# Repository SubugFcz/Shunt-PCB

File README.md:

# Shunt-PCB
Shunt PCB Design for GTSR

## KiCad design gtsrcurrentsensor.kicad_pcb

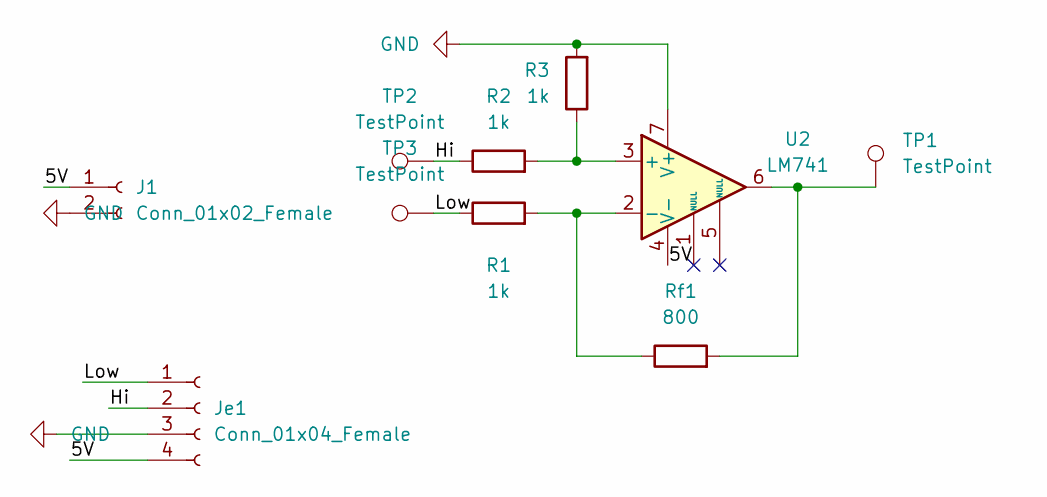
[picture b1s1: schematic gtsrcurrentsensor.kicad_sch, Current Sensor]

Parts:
J1: Conn_01x02_Female; Molex_Micro-Fit_3.0_43650-0215_1x02_P3.00mm_Vertical
Je1: Conn_01x04_Female; Molex_Micro-Fit_3.0_43650-0415_1x04_P3.00mm_Vertical
R1, R2, R3: 1k; R_Axial_DIN0207_L6.3mm_D2.5mm_P7.62mm_Horizontal
Rf1: 800; R_Axial_DIN0207_L6.3mm_D2.5mm_P7.62mm_Horizontal
TP1, TP2, TP3: TestPoint; gtsr-connector-KEYSTONE_5001_0
U2: LM741; DIP-8_W7.62mm

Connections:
/5V: J1.1, Je1.4, U2.4 (V-)
/Hi: Je1.2, R2.1, TP2.1
/Low: Je1.1, R1.1, TP3.1
GND: J1.2, Je1.3, R3.2, U2.7 (V+)
unnamed: R1.2, Rf1.1, U2.2 (-)
unnamed: R2.2, R3.1, U2.3 (+)
unnamed: Rf1.2, TP1.1, U2.6

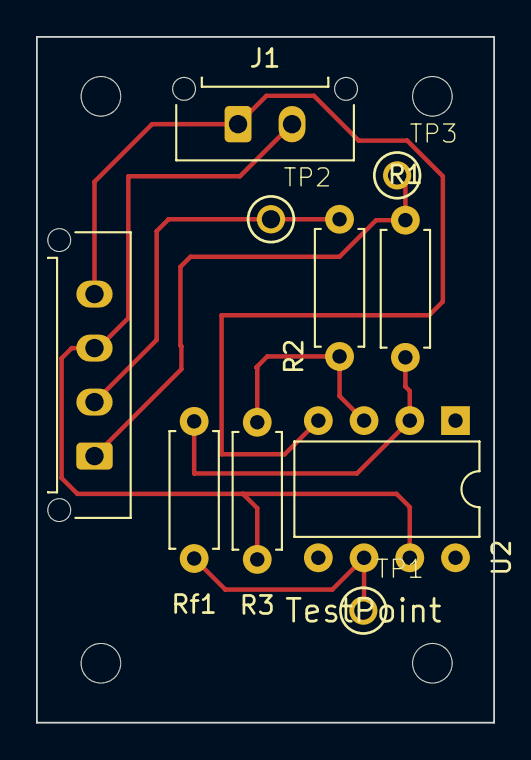
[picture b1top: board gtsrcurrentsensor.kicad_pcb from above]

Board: 2 copper layers, 25.4 x 38.1 mm, 10 parts (0 on the bottom side), 7 nets.

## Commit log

2023-07-18 Initial Upload
